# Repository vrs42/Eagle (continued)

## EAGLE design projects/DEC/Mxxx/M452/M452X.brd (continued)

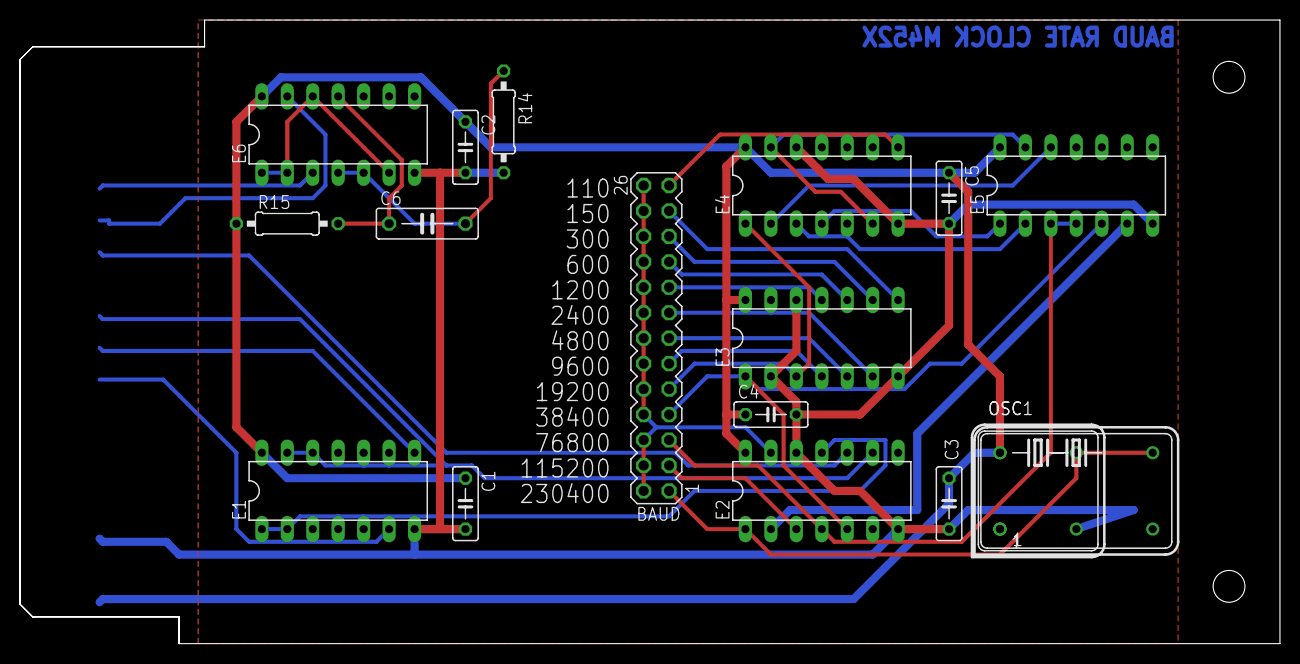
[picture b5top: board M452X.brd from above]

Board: 2 copper layers, 125.7 x 62.2 mm, 19 parts (0 on the bottom side), 31 nets.
